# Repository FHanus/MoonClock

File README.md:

## MoonClock C version

MoonClock website - https://moonclock.com

This fork is translation of the original app into smoother C language.

## You have received and unboxed your MoonClock. Congratulations!

What now?

1. Power your MoonClock.

2. On any device, open Wi-Fi connections and you should see "MoonClock Configuration" access point, tap it and a website should open. If a website doesn't open, open browser and enter "192.168.4.1" in the address bar.

3. Set up a Wi-Fi connection and if you want to, edit any of the settings in the main tab and then press update.

That's all!

## Want more to know all the possible options?

* app_choice
```sh
BlockHeight \ CryptoApp \ Difficulty \ Fees \ Halving \ MarketCap \ MoscowTimeApp \ TimeApp
```
* crypto_choice
```sh
cardano \ algorand \ baked-token \ bitcoin \ chain \ dogecoin \ ethereum \ kusama \ litecoin \ polkadot \ thorchain \ verasity
```
* fiat_choice
```sh
eur \ gbp \ usd
```
* timezone_choice
```sh
https://sites.google.com/a/usapiens.com/opnode/time-zones
```
* contrast_after_sunrise_choice 
```sh
0 - 255
```
* contrast_after_sunset_choice
```sh
0 - 255
```
* hide_seconds
```sh
true \ false
```

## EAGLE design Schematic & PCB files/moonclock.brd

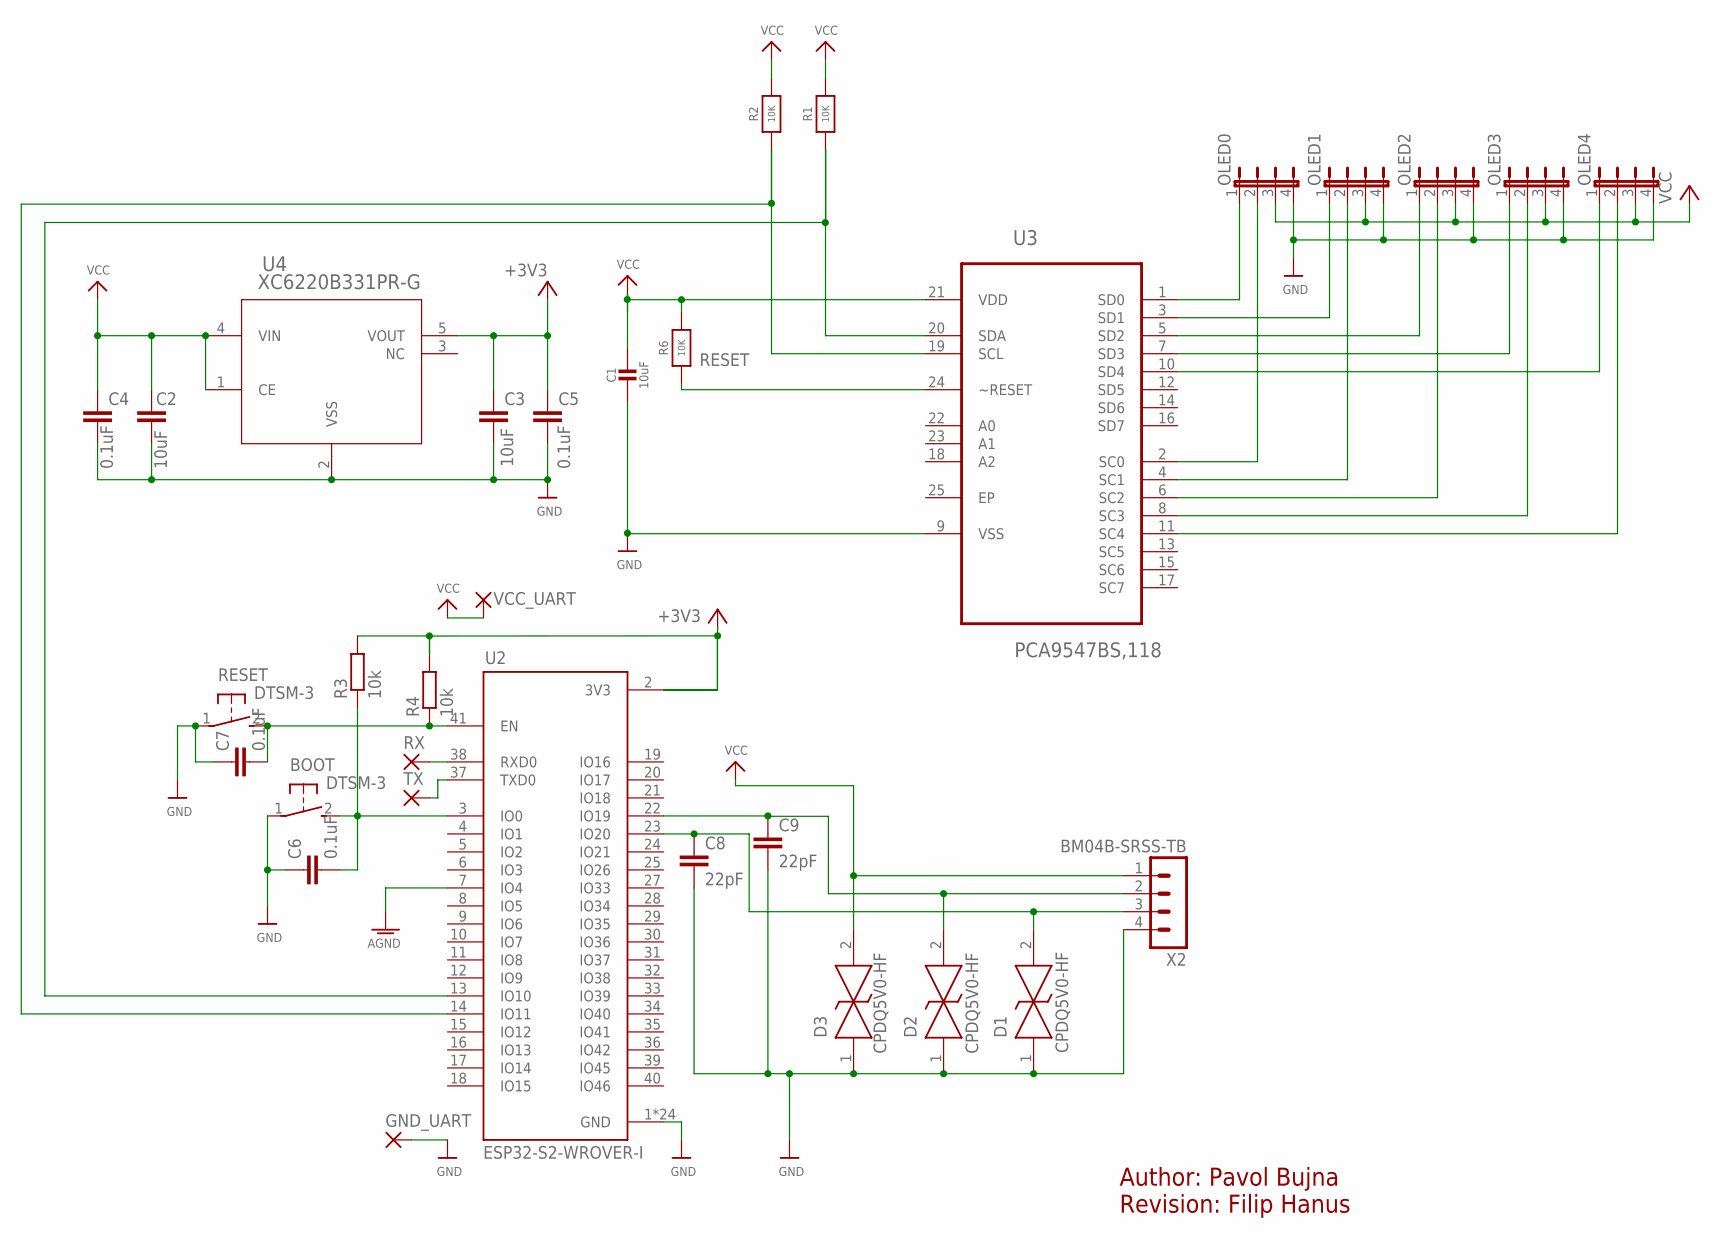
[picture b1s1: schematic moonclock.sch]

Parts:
BOOT: DTSM-3
C1: 10uF; 0805-NO
C2, C3: 10uF; C0805
C4, C5, C6, C7: 0.1uF; C0805
C8, C9: 22pF; C0805
D1, D2, D3: CPDQ5V0-HF; MBTB-D-SOD-923F-IMP-0402
GND_UART: SMD2; SMD1,27-2,54
OLED0, OLED1, OLED2, OLED3, OLED4: JP4E; JP4
R1, R2: 10K; 0805-NO
R3, R4: 10k; R0805
R6: 10K; _0805MP
RESET: DTSM-3
RX: SMD2; SMD1,27-2,54
TX: SMD2; SMD1,27-2,54
U2: ESP32-S2-WROVER-I
U3: PCA9547BS,118; QFN50P400X400X100-25N
U4: XC6220B331PR-G; SOT-89-5_TOR
VCC_UART: SMD2; SMD1,27-2,54
X2: BM04B-SRSS-TB

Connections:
+3V3: C3.1, C5.1, R3.2, R4.2, U4.5 (VOUT)
AGND: U2.7 (IO4)
D+: C8.1, D1.2 (A), U2.23 (IO20), X2.3
D-: C9.1, D2.2 (A), U2.22 (IO19), X2.2
GND: BOOT.1, C1.2, C2.2, C3.2, C4.2, C5.2, C6.1, C7.1, C8.2, C9.2, D1.1 (K), D2.1 (K), D3.1 (K), GND_UART.1, OLED0.4, OLED1.4, OLED2.4, OLED3.4, OLED4.4, RESET.1, U2.1 (GND), U2.26 (GND), U2.42 (GND), U2.43.1 (GND), U2.43.2 (GND), U2.43.3 (GND), U2.43.4 (GND), U2.43.5 (GND), U2.43.6 (GND), U2.43.7 (GND), U2.43.8 (GND), U2.43.9 (GND), U2.43.10 (GND), U2.43.11 (GND), U2.43.12 (GND), U2.43.13 (GND), U2.43.14 (GND), U2.43.15 (GND), U2.43.16 (GND), U2.43.17 (GND), U2.43.18 (GND), U2.43.19 (GND), U2.43.20 (GND), U2.43.21 (GND), U3.9 (VSS), U4.2 (VSS), X2.4
unnamed: R1.1, U2.13 (IO10), U3.20 (SDA)
unnamed: R2.1, U2.14 (IO11), U3.19 (SCL)
unnamed: OLED0.1, U3.1 (SD0)
unnamed: TX.1, U2.37 (TXD0)
unnamed: RX.1, U2.38 (RXD0)
unnamed: OLED1.1, U3.3 (SD1)
unnamed: BOOT.2, C6.2, R3.1, U2.3 (IO0)
unnamed: OLED2.1, U3.5 (SD2)
unnamed: C7.2, R4.1, RESET.2, U2.41 (EN)
unnamed: OLED3.1, U3.7 (SD3)
unnamed: OLED4.1, U3.10 (SD4)
unnamed: OLED0.2, U3.2 (SC0)
unnamed: OLED1.2, U3.4 (SC1)
unnamed: OLED2.2, U3.6 (SC2)
unnamed: OLED3.2, U3.8 (SC3)
unnamed: OLED4.2, U3.11 (SC4)
RESET: R6.1, U3.24 (~RESET)
VCC: C1.1, C2.1, C4.1, D3.2 (A), OLED0.3, OLED1.3, OLED2.3, OLED3.3, OLED4.3, R1.2, R2.2, R6.2, U3.21 (VDD), U4.1 (CE), U4.4 (VIN), VCC_UART.1, X2.1

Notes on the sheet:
Author: Pavol Bujna Revision: Filip Hanus

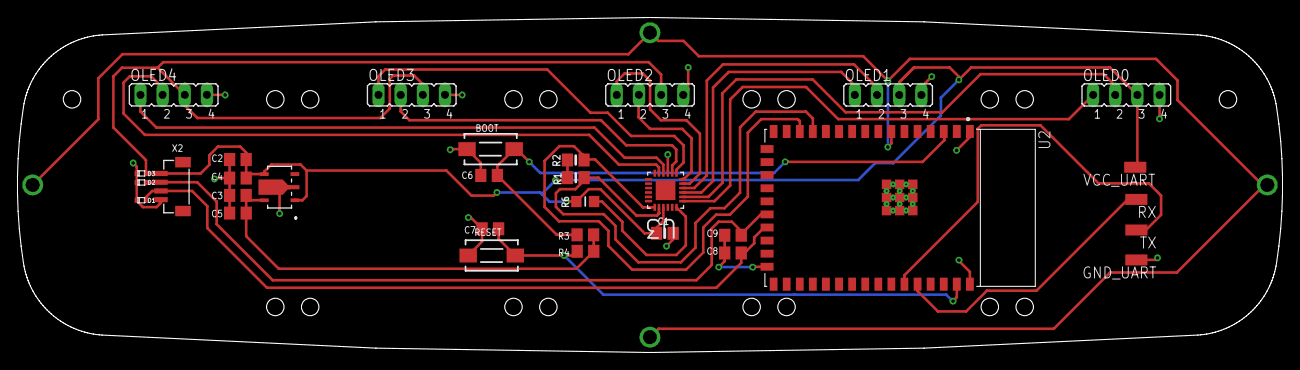
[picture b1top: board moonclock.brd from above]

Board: 2 copper layers, 145.0 x 38.4 mm, 32 parts (0 on the bottom side), 22 nets.

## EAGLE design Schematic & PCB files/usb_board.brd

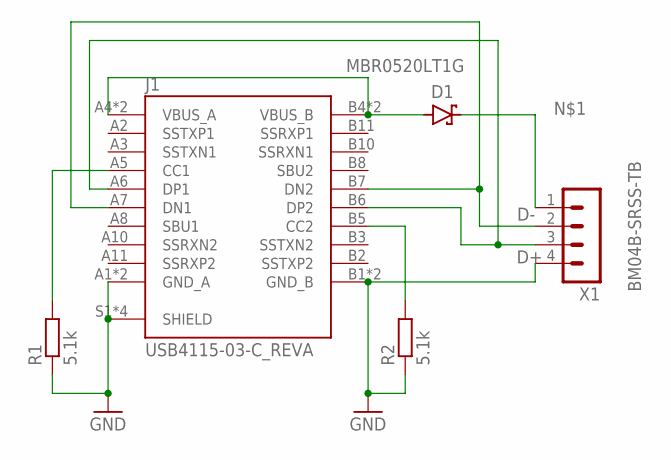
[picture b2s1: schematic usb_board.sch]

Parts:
D1: MBR0520LT1G; SODFL3718X115
J1: USB4115-03-C_REVA; GCT_USB4115-03-C_REVA
R1, R2: 5.1k; R0805
X1: BM04B-SRSS-TB

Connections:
D+: J1.A6 (DP1), J1.B6 (DP2), X1.3
D-: J1.A7 (DN1), J1.B7 (DN2), X1.2
GND: J1.A1 (GND_A), J1.A12 (GND_A), J1.B1 (GND_B), J1.B12 (GND_B), J1.S1 (SHIELD), J1.S2 (SHIELD), J1.S3 (SHIELD), J1.S4 (SHIELD), R1.1, R2.1, X1.4
unnamed: D1.1 (C), X1.1
unnamed: J1.A5 (CC1), R1.2
unnamed: J1.B5 (CC2), R2.2
VCC: D1.2 (A), J1.A4 (VBUS_A), J1.A9 (VBUS_A), J1.B4 (VBUS_B), J1.B9 (VBUS_B)

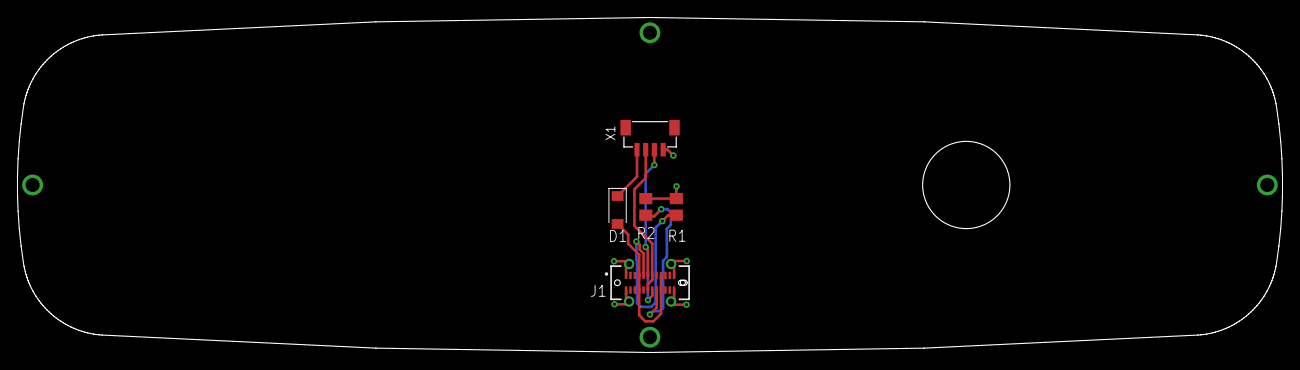
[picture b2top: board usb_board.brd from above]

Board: 2 copper layers, 145.0 x 38.4 mm, 5 parts (0 on the bottom side), 7 nets.

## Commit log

2022-07-31 C code first version
2022-08-12 Fixing up and polishing the code
    Full release preparations. Adding comments, fixing up debug messages, clearing functions for utils
2022-08-15 AutoContrast integration
2022-08-25 Add remaining comments, edit WiFi manager function, change time fetch function for faster functionality
2022-08-25 Comments
    Added final comments
2022-08-25 Fix timeout caused by short password
2022-08-31 Finished firmware, debugged
    * Fixed a couple of issues with the runtime
    * Created software update tool
2022-09-01 bug fixes
2022-09-04 Updated EAGLE files
2022-10-05 PCB
    feat: MoonClock add schematics and pcb files

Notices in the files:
parts and their libraries:
microbuilder: This work is placed in the public domain, and may be freely used for commercial and non-commercial work with the following conditions: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
COPYRIGHT: Copyright (C) 2022 Ultra Librarian. All rights reserved.
